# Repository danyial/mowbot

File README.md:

# MowBot

> **Work in Progress** — This project is under active development.
> Features may be incomplete, untested, or change without notice.

DIY robotic lawnmower powered by ROS2, Docker, and an ESP32 motor controller.
Runs on a Raspberry Pi 4 with RTK-GPS (UM980), IMU (MPU6050), and a
Next.js 16 web interface for monitoring and control.

## Architecture

All services run as Docker containers with `network_mode: host` for ROS2 DDS discovery.

| Service | Description |
|---------|-------------|
| **micro-ros-agent** | Serial bridge to ESP32 motor controller |
| **gnss** | NMEA NavSat driver for UM980 RTK-GPS |
| **ntrip** | RTCM3 correction data via str2str |
| **imu** | MPU6050 inertial measurement unit |
| **nav** | Nav2 navigation stack + EKF sensor fusion |
| **rosbridge** | WebSocket bridge between ROS2 and the web UI |
| **web** | Next.js 16 control dashboard (PWA) |

```
Browser (Phone/Laptop)
    |
    |  HTTP :3000
    v
 [web] ── /rosbridge (WebSocket proxy) ──> [rosbridge] :9090
                                                |
                                             ROS2 DDS
                                                |
                      ┌─────────┬──────────┬────┴────┬─────────┐
                   [gnss]    [imu]      [nav]   [ntrip]  [micro-ros-agent]
                     |         |                   |            |
                /dev/ttyGNSS  I2C             NTRIP Base    /dev/ttyAMA0
                  (UM980)   (MPU6050)          Station        (ESP32)
```

## Quickstart

### Prerequisites

- Raspberry Pi 4 (4/8 GB) with Ubuntu 22.04 or Raspberry Pi OS
- ESP32 with flashed firmware (see `firmware/`)
- UM980 GNSS module (CH341 USB)
- GY-521 IMU module (I2C)
- RTK base station with NTRIP access

### Installation

```bash
git clone https://github.com/danyial/mowbot.git
cd mowbot
chmod +x setup.sh
./setup.sh
```

### Configuration

1. Edit `.env` — verify device paths (`/dev/ttyAMA0`, `/dev/ttyGNSS`)
2. Edit `config/ntrip.env` — set your RTK base station credentials

### udev Rules

The setup script installs udev rules automatically. If you skipped `setup.sh` or need to install them manually:

```bash
sudo cp udev/99-mower.rules /etc/udev/rules.d/
sudo udevadm control --reload-rules
sudo udevadm trigger
```

This creates persistent symlinks for the USB devices:

| Device | Symlink | Hardware |
|--------|---------|----------|
| CH341 (UM980) | `/dev/ttyGNSS` | GNSS receiver |

Without these rules, the device paths may change on every reboot (e.g. `/dev/ttyUSB0` vs `/dev/ttyUSB1`), which would break the Docker container device mappings.

The ESP32 motor controller is wired to the Pi via HAT-internal UART (GPIO14/15) and exposed as `/dev/ttyAMA0` — no udev symlink needed.

### Start

```bash
docker compose up -d
```

### Web UI

Open `http://<pi-ip>:3000` or `http://mower.local:3000` (if mDNS is available).

The app can be installed as a PWA on your phone ("Add to Home Screen").

### Logs

```bash
docker compose logs -f web
docker compose logs -f gnss
docker compose logs -f micro-ros-agent
```

### Stop

```bash
docker compose down
```

## Local Build

By default, `docker compose up` pulls pre-built images from `ghcr.io/danyial/mowbot/`.

To build locally instead (e.g. after modifying a Dockerfile):

```bash
docker compose -f docker-compose.yml -f docker-compose.build.yml build
docker compose -f docker-compose.yml -f docker-compose.build.yml up -d
```

## Project Structure

```
mowbot/
├── docker-compose.yml          # Pre-built images (default)
├── docker-compose.build.yml    # Local build overrides
├── .env.example                # Host configuration template
├── setup.sh                    # First-time setup (Docker, udev, I2C)
│
├── docker/                     # Dockerfiles for all services
│   ├── ros2-base/
│   ├── micro-ros-agent/
│   ├── gnss/
│   ├── ntrip/
│   ├── imu/
│   ├── nav/
│   ├── rosbridge/
│   └── web/
│
├── config/                     # ROS2 + service configuration
│   ├── ntrip.env               # NTRIP credentials
│   ├── ekf.yaml                # EKF sensor fusion
│   ├── nav2_params.yaml        # Navigation parameters
│   ├── robot.yaml              # Robot dimensions and limits
│   ├── nmea.yaml               # GNSS driver config
│   ├── cyclonedds.xml          # DDS middleware config
│   └── mower_nav_launch.py     # ROS2 launch file
│
├── web/                        # Next.js 16 web application
│   ├── app/                    # App Router pages + API routes
│   ├── components/             # React components
│   ├── lib/                    # ROS client, stores, utilities
│   └── server.mjs              # Custom server with WS proxy
│
├── firmware/                   # ESP32 micro-ROS firmware
│   ├── src/main.cpp            # Motor controller (PlatformIO)
│   ├── platformio.ini
│   └── flash_esp32.sh          # Flash script (stops Docker first)
│
├── udev/                       # Device symlink rules
│   └── 99-mower.rules
│
└── docs/                       # Documentation (WIP)
```

## Hardware

| Component | Model | Interface | Purpose |
|-----------|-------|-----------|---------|
| SBC | Raspberry Pi 4 (4/8 GB) | — | Main computer |
| Motor Controller | ESP32 DOIT DevKit V1 | USB Serial | Differential drive via ESCs |
| GNSS | UM980 | USB Serial (CH341) | RTK positioning (cm accuracy) |
| IMU | GY-521 (MPU6050) | I2C | Orientation and acceleration |
| ESCs | Brushed RC ESCs (x2) | PWM from ESP32 | Left/right motor control |

## ESP32 Firmware

The ESP32 runs a micro-ROS node that subscribes to `/cmd_vel` and drives two ESCs.
It includes a 500ms watchdog — motors stop automatically if no commands are received.

To flash:

```bash
cd firmware
./flash_esp32.sh    # Stops micro-ros-agent, flashes, restarts
```

Or manually with PlatformIO:

```bash
cd firmware
pio run --target upload
```

## License

[MIT](LICENSE)

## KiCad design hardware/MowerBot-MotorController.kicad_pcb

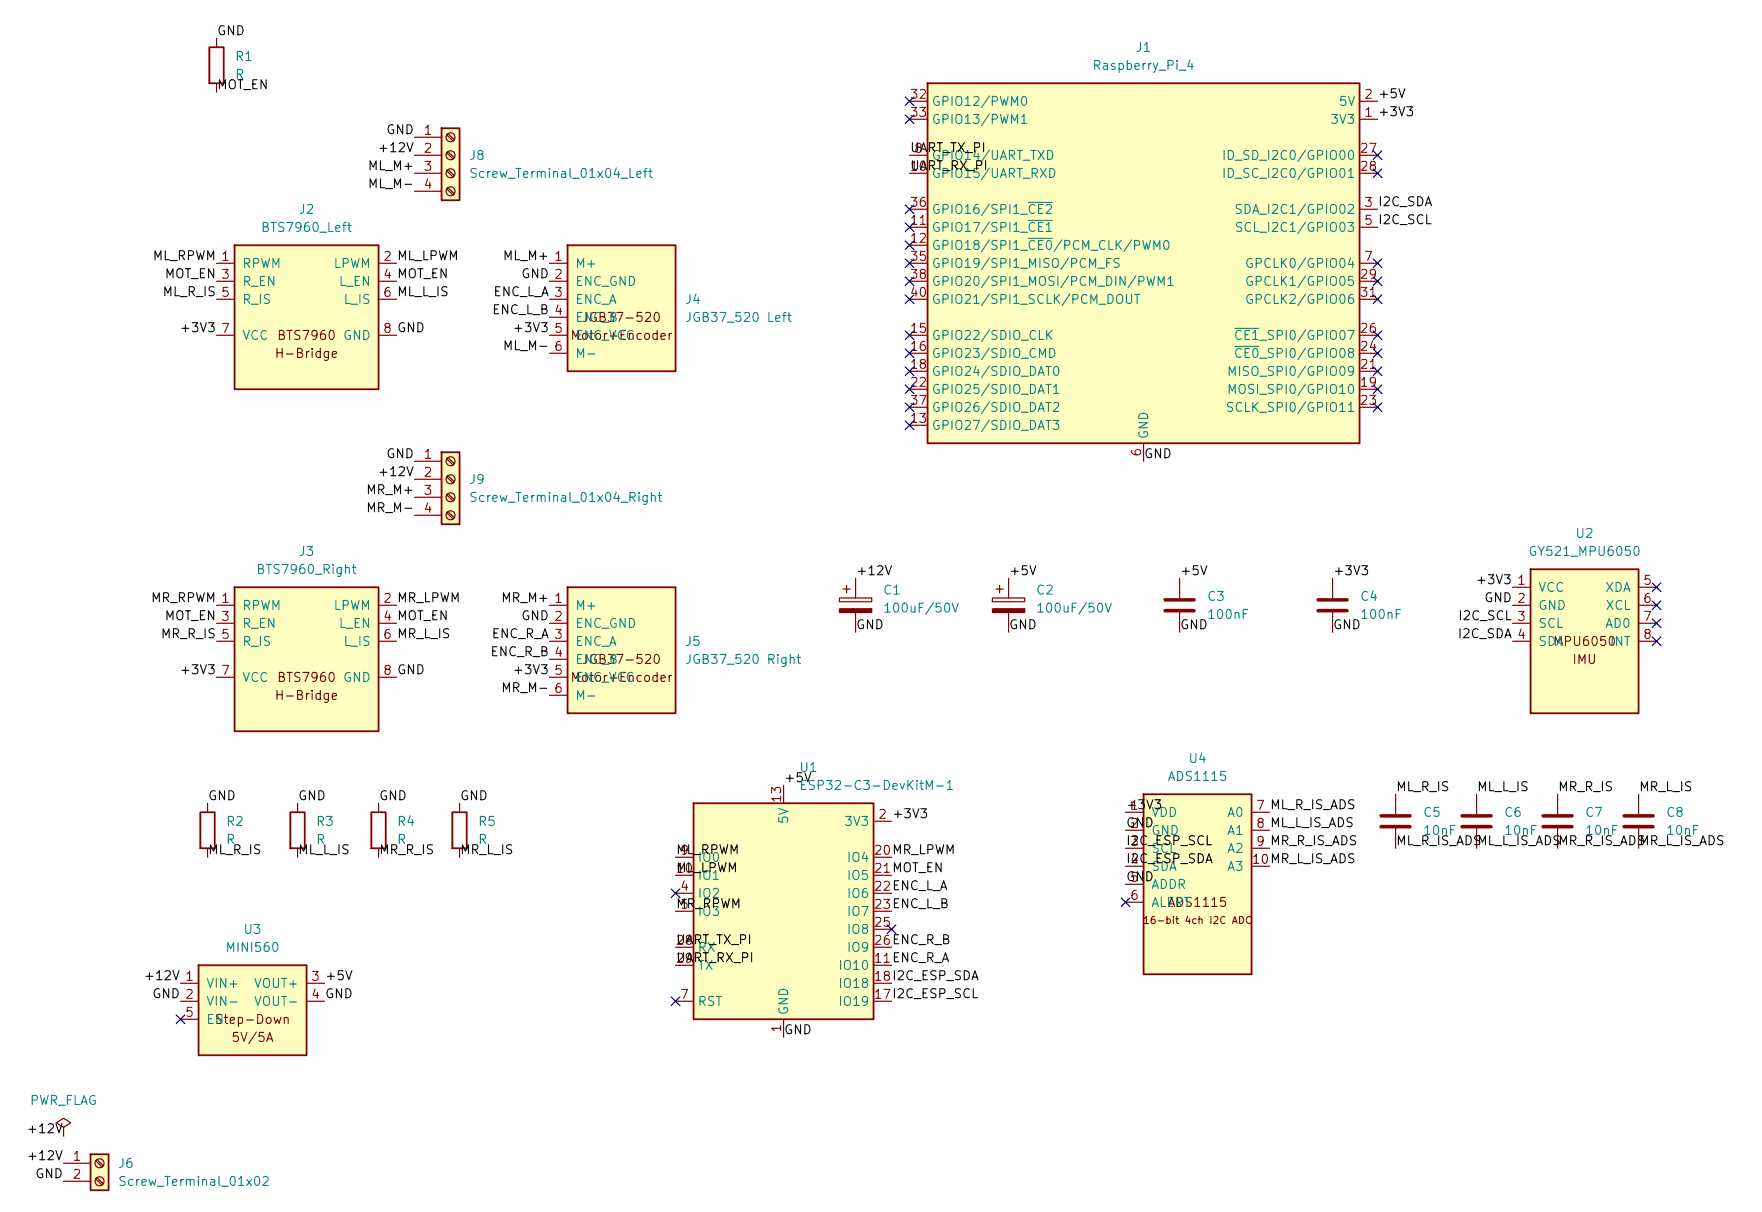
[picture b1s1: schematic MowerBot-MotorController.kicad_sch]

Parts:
C1, C2: 100uF/50V; CP_Radial_D8.0mm_P3.50mm
C3, C4: 100nF; C_0805_2012Metric
C5, C6, C7, C8: 10nF; C_0805_2012Metric
J1: Raspberry_Pi_4; PinSocket_2x20_P2.54mm_Vertical
J2: BTS7960_Left; BTS7960
J3: BTS7960_Right; BTS7960
J4: JGB37_520 Left; JGB37_520
J5: JGB37_520 Right; JGB37_520
J6: Screw_Terminal_01x02; TerminalBlock_Phoenix_MKDS-1,5-2-5.08_1x02_P5.08mm_Horizont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
J8: Screw_Terminal_01x04_Left; TerminalBlock_Phoenix_MKDS-1,5-4-5.08_1x04_P5.08mm_Horizont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
J9: Screw_Terminal_01x04_Right; TerminalBlock_Phoenix_MKDS-1,5-4-5.08_1x04_P5.08mm_Horizont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
R1, R2, R3, R4, R5: R; R_0805_2012Metric
U1: ESP32-C3-DevKitM-1
U2: GY521_MPU6050
U3: MINI560
U4: ADS1115

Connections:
/+3V3: C4.1, J1.1 (3V3), J1.17 (3V3), J2.7 (VCC), J3.7 (VCC), J4.5 (ENC_VCC), J5.5 (ENC_VCC), U1.2 (3V3), U1.3 (3V3), U2.1 (VCC), U4.1 (VDD)
/+5V: C2.1, C3.1, J1.2 (5V), J1.4 (5V), U1.13 (5V), U1.14 (5V), U3.3 (VOUT+)
/+12V: C1.1, J6.1, J8.2, J9.2, U3.1 (VIN+)
/ENC_L_A: J4.3 (ENC_A), U1.22 (IO6)
/ENC_L_B: J4.4 (ENC_B), U1.23 (IO7)
/ENC_R_A: J5.3 (ENC_A), U1.11 (IO10)
/ENC_R_B: J5.4 (ENC_B), U1.26 (IO9)
/GND: C1.2, C2.2, C3.2, C4.2, J1.6 (GND), J1.9 (GND), J1.14 (GND), J1.20 (GND), J1.25 (GND), J1.30 (GND), J1.34 (GND), J1.39 (GND), J2.8 (GND), J3.8 (GND), J4.2 (ENC_GND), J5.2 (ENC_GND), J6.2, J8.1, J9.1, R1.1, R2.1, R3.1, R4.1, R5.1, U1.1 (GND), U1.6 (GND), U1.8 (GND), U1.12 (GND), U1.15 (GND), U1.16 (GND), U1.19 (GND), U1.24 (GND), U1.27 (GND), U1.30 (GND), U2.2 (GND), U3.2 (VIN-), U3.4 (VOUT-), U4.2 (GND), U4.5 (ADDR)
/I2C_ESP_SCL: U1.17 (IO19), U4.3 (SCL)
/I2C_ESP_SDA: U1.18 (IO18), U4.4 (SDA)
/I2C_SCL: J1.5 (SCL_I2C1/GPIO03), U2.3 (SCL)
/I2C_SDA: J1.3 (SDA_I2C1/GPIO02), U2.4 (SDA)
/ML_LPWM: J2.2 (LPWM), U1.10 (IO1)
/ML_L_IS: C6.1, J2.6 (L_IS), R3.2
/ML_L_IS_ADS: C6.2, U4.8 (A1)
/ML_M+: J4.1 (M+), J8.3
/ML_M-: J4.6 (M-), J8.4
/ML_RPWM: J2.1 (RPWM), U1.9 (IO0)
/ML_R_IS: C5.1, J2.5 (R_IS), R2.2
/ML_R_IS_ADS: C5.2, U4.7 (A0)
/MOT_EN: J2.3 (R_EN), J2.4 (L_EN), J3.3 (R_EN), J3.4 (L_EN), R1.2, U1.21 (IO5)
/MR_LPWM: J3.2 (LPWM), U1.20 (IO4)
/MR_L_IS: C8.1, J3.6 (L_IS), R5.2
/MR_L_IS_ADS: C8.2, U4.10 (A3)
/MR_M+: J5.1 (M+), J9.3
/MR_M-: J5.6 (M-), J9.4
/MR_RPWM: J3.1 (RPWM), U1.5 (IO3)
/MR_R_IS: C7.1, J3.5 (R_IS), R4.2
/MR_R_IS_ADS: C7.2, U4.9 (A2)
/UART_RX_PI: J1.10 (GPIO15/UART_RXD), U1.29 (TX)
/UART_TX_PI: J1.8 (GPIO14/UART_TXD), U1.28 (RX)

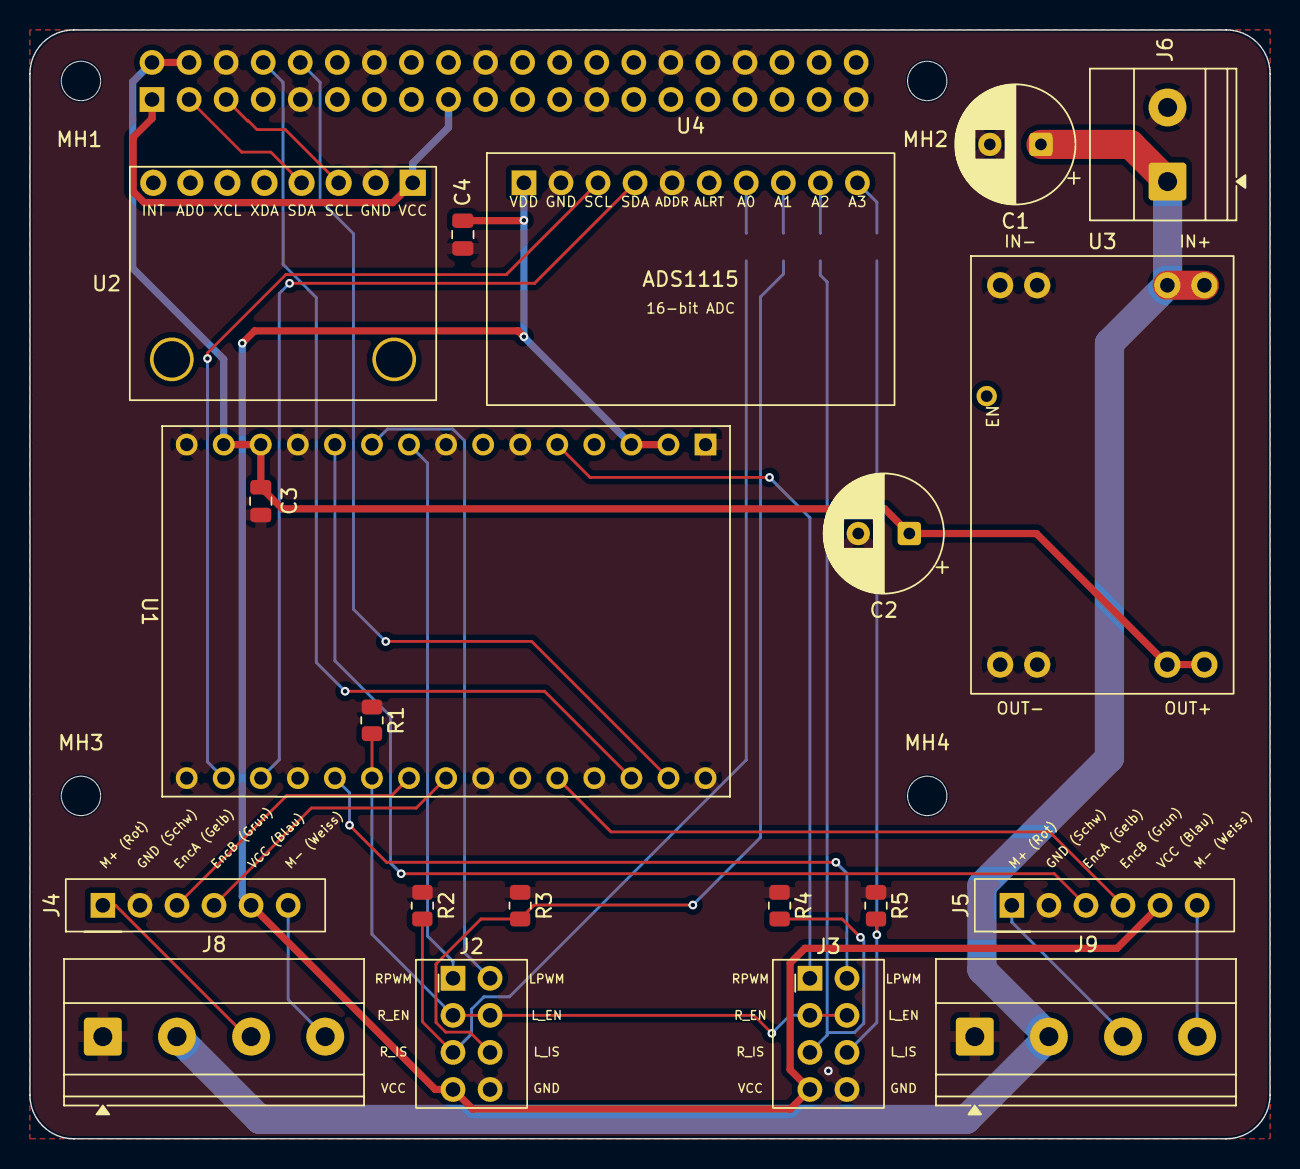
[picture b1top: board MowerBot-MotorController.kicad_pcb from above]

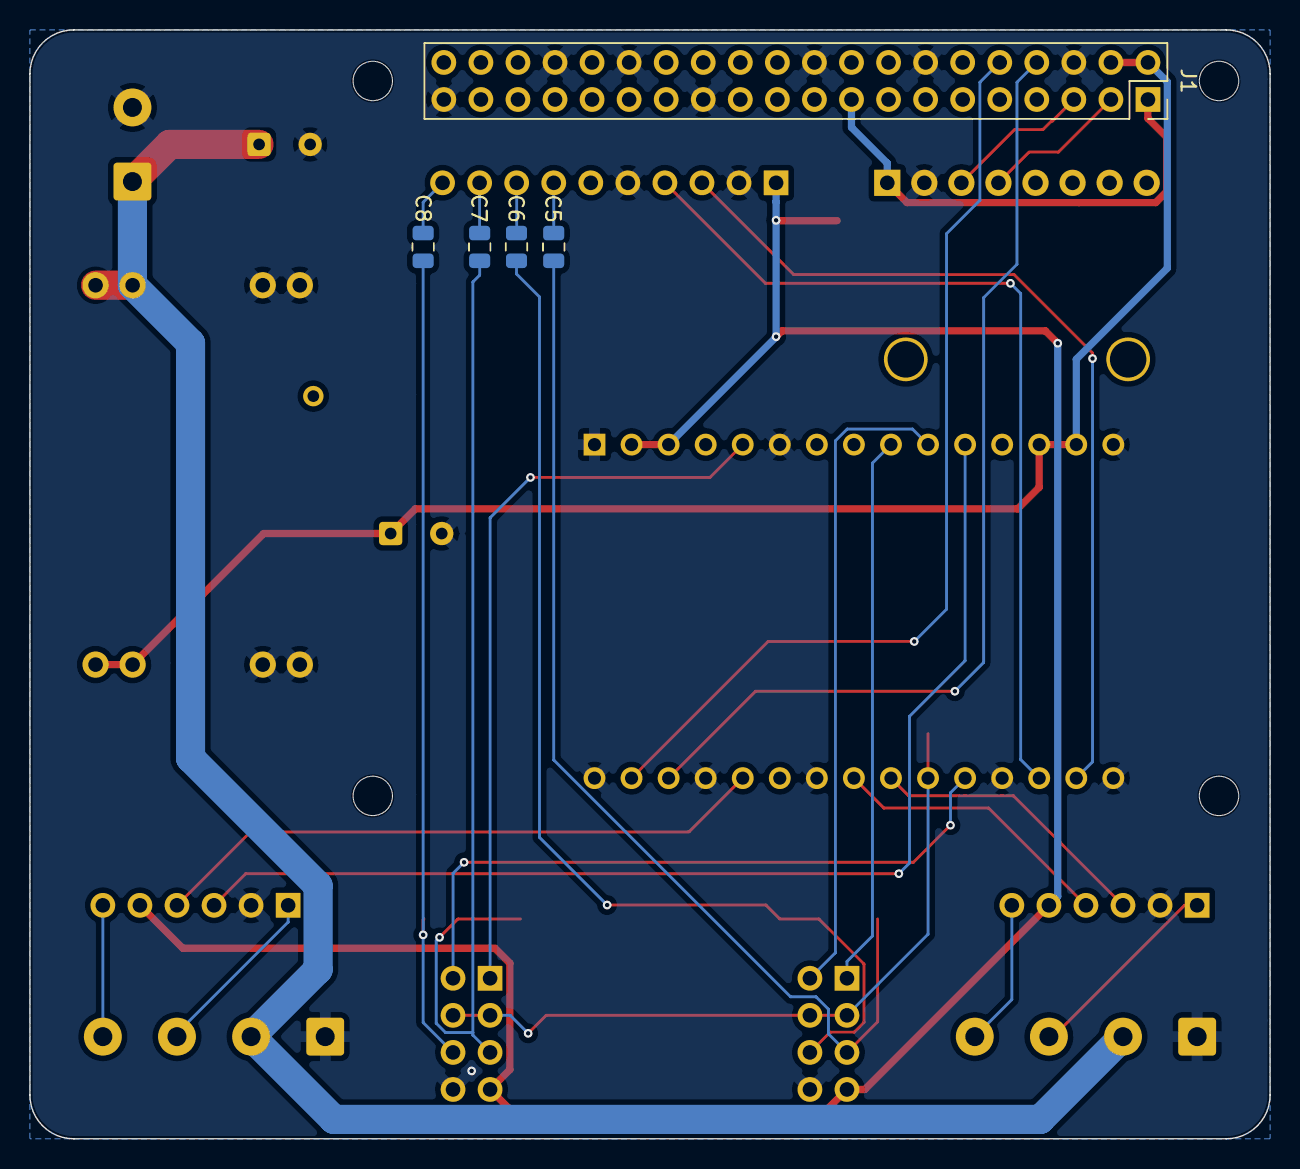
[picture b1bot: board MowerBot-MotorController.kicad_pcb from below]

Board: 2 copper layers, 85.0 x 76.0 mm, 29 parts (5 on the bottom side), 31 nets.

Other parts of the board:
MH1, MH2, MH3, MH4: MountingHole_2.75mm; MountingHole_2.7mm_M2.5

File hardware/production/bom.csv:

Designator,Footprint,Quantity,Value,LCSC Part #
"C1, C2",CP_Radial_D8.0mm_P3.50mm,2,100uF/50V,
"C3, C4",0805,2,100nF,
"C5, C6, C7, C8",0805,4,10nF,
J1,PinSocket_2x20_P2.54mm_Vertical,1,Raspberry_Pi_4,
J2,BTS7960,1,BTS7960_Left,
J3,BTS7960,1,BTS7960_Right,
J4,JGB37_520,1,JGB37_520 Left,
J5,JGB37_520,1,JGB37_520 Right,
J6,"TerminalBlock_Phoenix_MKDS-1,5-2-5.08_1x02_P5.08mm_Horizontal",1,Screw_Terminal_01x02,
J8,"TerminalBlock_Phoenix_MKDS-1,5-4-5.08_1x04_P5.08mm_Horizontal",1,Screw_Terminal_01x04_Left,
J9,"TerminalBlock_Phoenix_MKDS-1,5-4-5.08_1x04_P5.08mm_Horizontal",1,Screw_Terminal_01x04_Right,
"R1, R2, R3, R4, R5",0805,5,R,
U1,ESP32-C3-DevKitM-1,1,ESP32-C3-DevKitM-1,
U2,GY521_MPU6050,1,GY521_MPU6050,
U3,MINI560,1,MINI560,
U4,ADS1115,1,ADS1115,

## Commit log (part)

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2026-03-23 Initial MowBot monorepo
2026-03-23 feat: use pre-built ghcr.io images, move build config to docker-compose.build.yml
2026-03-23 docs: add udev rules section to README
2026-03-24 fix: set NEXT_PUBLIC_ROSBRIDGE_URL at build time in web Dockerfile
    NEXT_PUBLIC_* variables are embedded into client code at build time by
    Next.js, not at runtime. Without this, the browser falls back to
    ws://mower.local:9090 instead of using the /rosbridge proxy path.
2026-03-24 feat: GeoJSON-based zone system with Turf.js
    Add multi-zone support for garden management:
    - Zone types: garden, mow, exclusion, corridor, dock
    - Manual polygon drawing on map (click-to-place points)
    - GPS boundary recording (with 0.5m min distance filter)
    - Full CRUD API at /api/zones (GeoJSON FeatureCollection)
    - Turf.js for geodesic area calculation, polygon validation,
2026-03-24 refactor: consolidate zone editing — remove move mode, add polygon drag
    - Remove separate move mode (EditMode 'move', MovingOverlay, move
    controls, active zone info panel) — all zone management now via
    'Zonen verwalten' panel
    - Add polygon drag-to-move in edit mode: grab the polygon fill area
    to reposition the entire zone, with live preview
    - Add moveAllEditingPoints store action for polygon drag offset
2026-03-24 fix: mission card layout, stop bug, add area stats
    - Horizontal expanded layout: details left (40%), map right (60%)
    - Show turns, perimeter area (m²), inner area (m²), angle, increment
    - Bigger map preview (h-64 instead of h-48)
    - Fix stop/pause/resume bug: actions now accept missionId parameter,
    activeMission auto-detected on fetchMissions, status persisted to server
    - Fix dashboard mission-status widget type error
2026-03-25 fix: larger mission preview map (448px) with better auto-zoom padding
2026-03-25 fix: generate perimeter passes around exclusion zones (holes)
    extractPerimeterPoints now iterates all polygon rings, not just the
    outer ring. Inner rings (holes from exclusion zones) get their own
    perimeter passes so the robot mows cleanly around obstacles.
2026-03-25 fix: remove auto-close threshold — polygon closes only via Fertig button
    - Remove 15m distance threshold that auto-closed polygon after 3 points
    (was triggering on every click in small gardens)
    - Remove 'Klick zum Schliessen' tooltip from first point
    - Remove zone-drawing-close-requested custom event and listener
    - Simplify ZoneDrawHandler to just addDrawingPoint on every click
    - Increase maxZoom from 22 to 24 for precise point placement
2026-03-25 fix: settings deep merge, cm sliders, fallback defaults
    - Deep merge config per section so new fields (robotLength, edgeClearance
    etc.) get default values when missing from saved config.json
    - Kettenabstand + Maehwerk-Breite changed from m Input to cm Slider
    (internally still stored in meters for ROS compatibility)
    - All new slider values use ?? fallback defaults to prevent missing
    thumbs when config fields don't exist yet
2026-03-25 feat: dock path (exit/entry line) + dock exit distance + routing fixes
    Zone system:
    - New zone type 'dockPath' (LineString) for dock exit/entry path
    - LineString geometry support in Zone interface, API, store, and layer
    - DrawingPreview shows Polyline for line zone types (min 2 points)
    - ZonePolygon renders LineString zones as Polyline with dash pattern
    - 'Ein-/Ausfahrt' option in zone menu with MoveRight icon
2026-03-25 fix: safe routing via edge projection — paths stay inside garden boundary
    Replace findBestPerimeterPath (nearest vertex) with safeRoute() that
    projects endpoints onto nearest polygon EDGE instead of vertex. This
    prevents straight-line connectors from cutting outside concave boundaries.
    - Add projectPointOntoRing() for perpendicular edge projection
    - Add safeRoute() that validates all connector segments
    - Add connectRingsWithSafeRoute() for MultiPolygon perimeter rings
2026-03-25 refactor: unified safeRoute with clearance enforcement for all path types
    Merge safeRouteDock() into safeRoute() with a unified insetArea parameter.
    The same clearance rules now apply to ALL connection types:
    - Stripe-to-stripe connections
    - Perimeter group connections
    - Dock exit/entry connections
    How it works:
2026-03-25 diag: motor impulse test at startup + LED status feedback
    Diagnostic firmware to identify where the chain breaks:
    - 10% motor impulse for 500ms at startup (tests ESC+PWM)
    - 3x LED flash after setup complete
    - LED blink 1000ms = waiting for agent
    - LED blink 500ms = agent connected, no cmd_vel
    - LED blink 100ms = receiving cmd_vel
2026-04-04 feat: KiCad PCB project for MowerBot Motor Controller
    Initial hardware design for the motor controller breakout board.
    Connects ESP32 DevKit V1 (38-pin) with 2x BTS7960 H-bridge modules
    and 2x JGB37-520 encoder motors.
    Schematic (15 components, 17 nets):
    - U1A/U1B: ESP32 DevKit V1 (2x 19-pin socket headers)
    - J1/J2: BTS7960 H-bridge connectors (6-pin: RPWM, LPWM, R_EN, L_EN, VCC, GND)
2026-04-04 feat: redesign PCB as Raspberry Pi HAT v2.0 (65x100mm)
    Complete KiCad project redesign for Raspberry Pi HAT form factor.
    Board specifications:
    - Size: 65x100mm (Pi HAT width, extended length)
    - 6x M2.5 mounting holes (4 Pi HAT standard + 2 chassis support)
    - GND copper pour on B.Cu
    - Stacking header for Pi GPIO pass-through
2026-04-14 chore: add project config
2026-04-14 docs: create roadmap (4 phases)
2026-04-14 docs(phase-3): research web visualization — CBOR retrofit risk + server.mjs probe
2026-04-14 feat(web/03-01): global CBOR retrofit with binary NaN scrubber
    Plan 03-01 of phase 3 (LD19 LiDAR web viz). Threads {compression,
    throttle_rate, queue_length} from the TOPICS registry through
    subscribe() into ROSLIB.Topic, flips compression:'cbor' globally, and
    adds a recursive NaN→null scrubber at the subscriber boundary so
    binary CBOR frames remain well-behaved (IEEE-754 NaN floats used to
    reach stores directly under CBOR because server.mjs's regex only
2026-04-14 docs(todos): capture tomorrow's work — deeper /lidar zoom + live SLAM map
    Two follow-ups from the 2026-04-14 session after phase 3 wrapped:
    - raise /lidar zoom clamp beyond 8× with smoother exponential feel
    - build a real occupancy-grid map during scanning (slam_toolbox
    candidate; gated on ESP32 /odom publisher which is still deferred)
2026-04-15 docs(04): research slam_toolbox live mapping — async config, TF, render, pitfalls
2026-04-15 docs(04): revise plan 01 per PLAN-CHECK findings
    Flag A: Plan-B fallback (EKF publish_tf:false + static odom->base_link) operationalized as conditional Task 7, triggered by run-plan-b resume signal if SC#4 drift probe fails. Flag B: canonical sshpa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
2026-04-15 feat(04-01): add slam_toolbox Dockerfile (Humble, CycloneDDS, pinned launch args)
    - ros:humble-ros-base + apt slam_toolbox + rmw_cyclonedds_cpp
    - CMD launches online_async with slam_params_file + use_sim_time:=false
    - cyclonedds.xml mounted at runtime via *ros-common /config volume
2026-04-15 docs(04-01): summary
2026-04-15 feat(04-02): add MapBitmap component + mount as ScanCanvas underlay on /lidar
    - map-bitmap.tsx: offscreen W*H backing canvas (putImageData once per /map identity)
    composited via drawImage onto visible canvas on every transform change
    - Nav2/rviz-style greyscale colormap (unknown 96/alpha-180, free 240, occ 20)
    - Defensive bounds check on info.width/height + data.length; console.warn on mismatch
    - v0 anchor limitation (Flag G) called out in file header — stationary-only
    - app/lidar/page.tsx: pass MapBitmap into ScanCanvas's underlay slot; wrapper div removed
2026-04-15 docs(04-02): summary
2026-04-15 fix(web/lidar): larger scan points (floor 4px, ceiling 9px)
    User feedback: points still hard to see even with 1 px black outline.
    Bump pointSize clamp from [2, 5] @ 0.25× zoom factor to [4, 9] @ 0.4×,
    roughly 4× visible area at default zoom.
2026-04-15 docs(quick-260415-fqf): task record + close todo
    Archive the cleanup task brief and move the source todo from
    pending/ to completed/.
2026-04-15 docs(audit): cross-phase UAT audit before milestone close
    9 open items grouped by testability:
    - Group A (8 items, ~10min, indoor stationary): Phase 4 UX + Phase 3 stale badge + 5min bufferedAmount
    - Group B (1 item, ~5min, Foxglove): Phase 3 layout import
    - Group C (1 item, outdoor 15min): Phase 3 SC#1 Core Value gate
    Plus 3 acknowledged design-deferred items not blocking milestone close.
2026-04-15 fix(web/lidar): flip display rotation sign (+π/2 not −π/2)
    Previous commit 0d35f07 applied the wrong rotation direction based on
    a misread of user feedback. Correct setup per user: LD19 mounted
    arrow-forward + cable-right, so scan angle 0 already renders at canvas
    3 o'clock. Rotating display by +π/2 (CCW 90° in canvas) moves
    3 o'clock → 12 o'clock, making mower-forward align with canvas-up
    as the operator expects. Map bitmap inherits the same rotation via
2026-04-15 docs: create milestone v2.2 roadmap (3 phases)
2026-04-15 docs(phase-06): UI design contract
2026-04-15 test(06-01): add server-upgrade regression + docker-adapter allowlist tests
    - server-upgrade.test.mjs: grep regression, single upgrade listener + /rosbridge + /logs/stream/ branch gate
    - docker-adapter.test.mjs: allowlist exports {listContainers, getContainer, getEvents}
    and getContainer facade allowlist {inspect, logs, modem}
    RED state expected: /logs/stream/ branch and docker-adapter.js not yet present — Plan 02 flips green.
2026-04-15 feat(06-02): add logs types + demux + since-preset pure modules
    - web/lib/types/logs.ts — ContainerSummary, LogFrame, SincePreset
    - web/lib/server/demux.mjs — pure 8-byte-frame demuxer (stdout/stderr)
    - web/lib/server/since-preset.mjs — preset → epoch-seconds (graceful null)
    - Deviation: runtime modules written as .mjs (not .ts) so node:test can
    import them without a build step. Test specifiers updated
    .js → .mjs. Task 1 step 4 authorized this. TypeScript route files
2026-04-15 feat(06-02): add /logs/stream/<id> branch to server.mjs upgrade handler
    Extends the existing single server.on('upgrade') listener — no second
    listener added (T-06-02 regression gate HOLDS, count === 1).
    Branch behavior:
    - Parses :id + ?since (preset allowlist) + ?tail (clamped 0..5000)
    - Validates id against live listContainers() — WS 1008 close if absent
    - inspect() to read Config.Tty; demuxes via container.modem.demuxStream
2026-04-15 feat(06-03): logs store + ContainerList + SincePresetChips + ConnectionBadge
    - useLogsStore: selectedContainerId / sincePreset / connectionState
    (latest-only, no storage layer, no timers — buffer lives in viewer ref)
    - ContainerList: one-shot /api/logs/containers hydrate + EventSource
    /api/logs/events for live updates (no polling timers); re-hydrates on
    start/resumed, mutates state map on die/destroy; Docker-unreachable
    banner (AlertTriangle + German copy) on hydrate 503
2026-04-15 feat(07-01): add yaw-drift-test.sh FUSE-02 validator
    - Parameterized DURATION arg (default 60, positive integer validated)
    - Fail-fast guard: exits 1 if /odometry/filtered absent from mower-nav
    - Quaternion→yaw via tf_transformations inside nav container
    - ±π unwrap handles wrap-around (no 359° false drift reports)
    - Single-line stdout: 'Δyaw = X.XX° over Ns — PASS|FAIL (<1°)' per D-17
    - Exit 0 on PASS (<1°), 1 on FAIL or precondition failure
2026-04-15 docs(07-03): summary — FUSE-03 badge wired, awaiting operator human-verify
